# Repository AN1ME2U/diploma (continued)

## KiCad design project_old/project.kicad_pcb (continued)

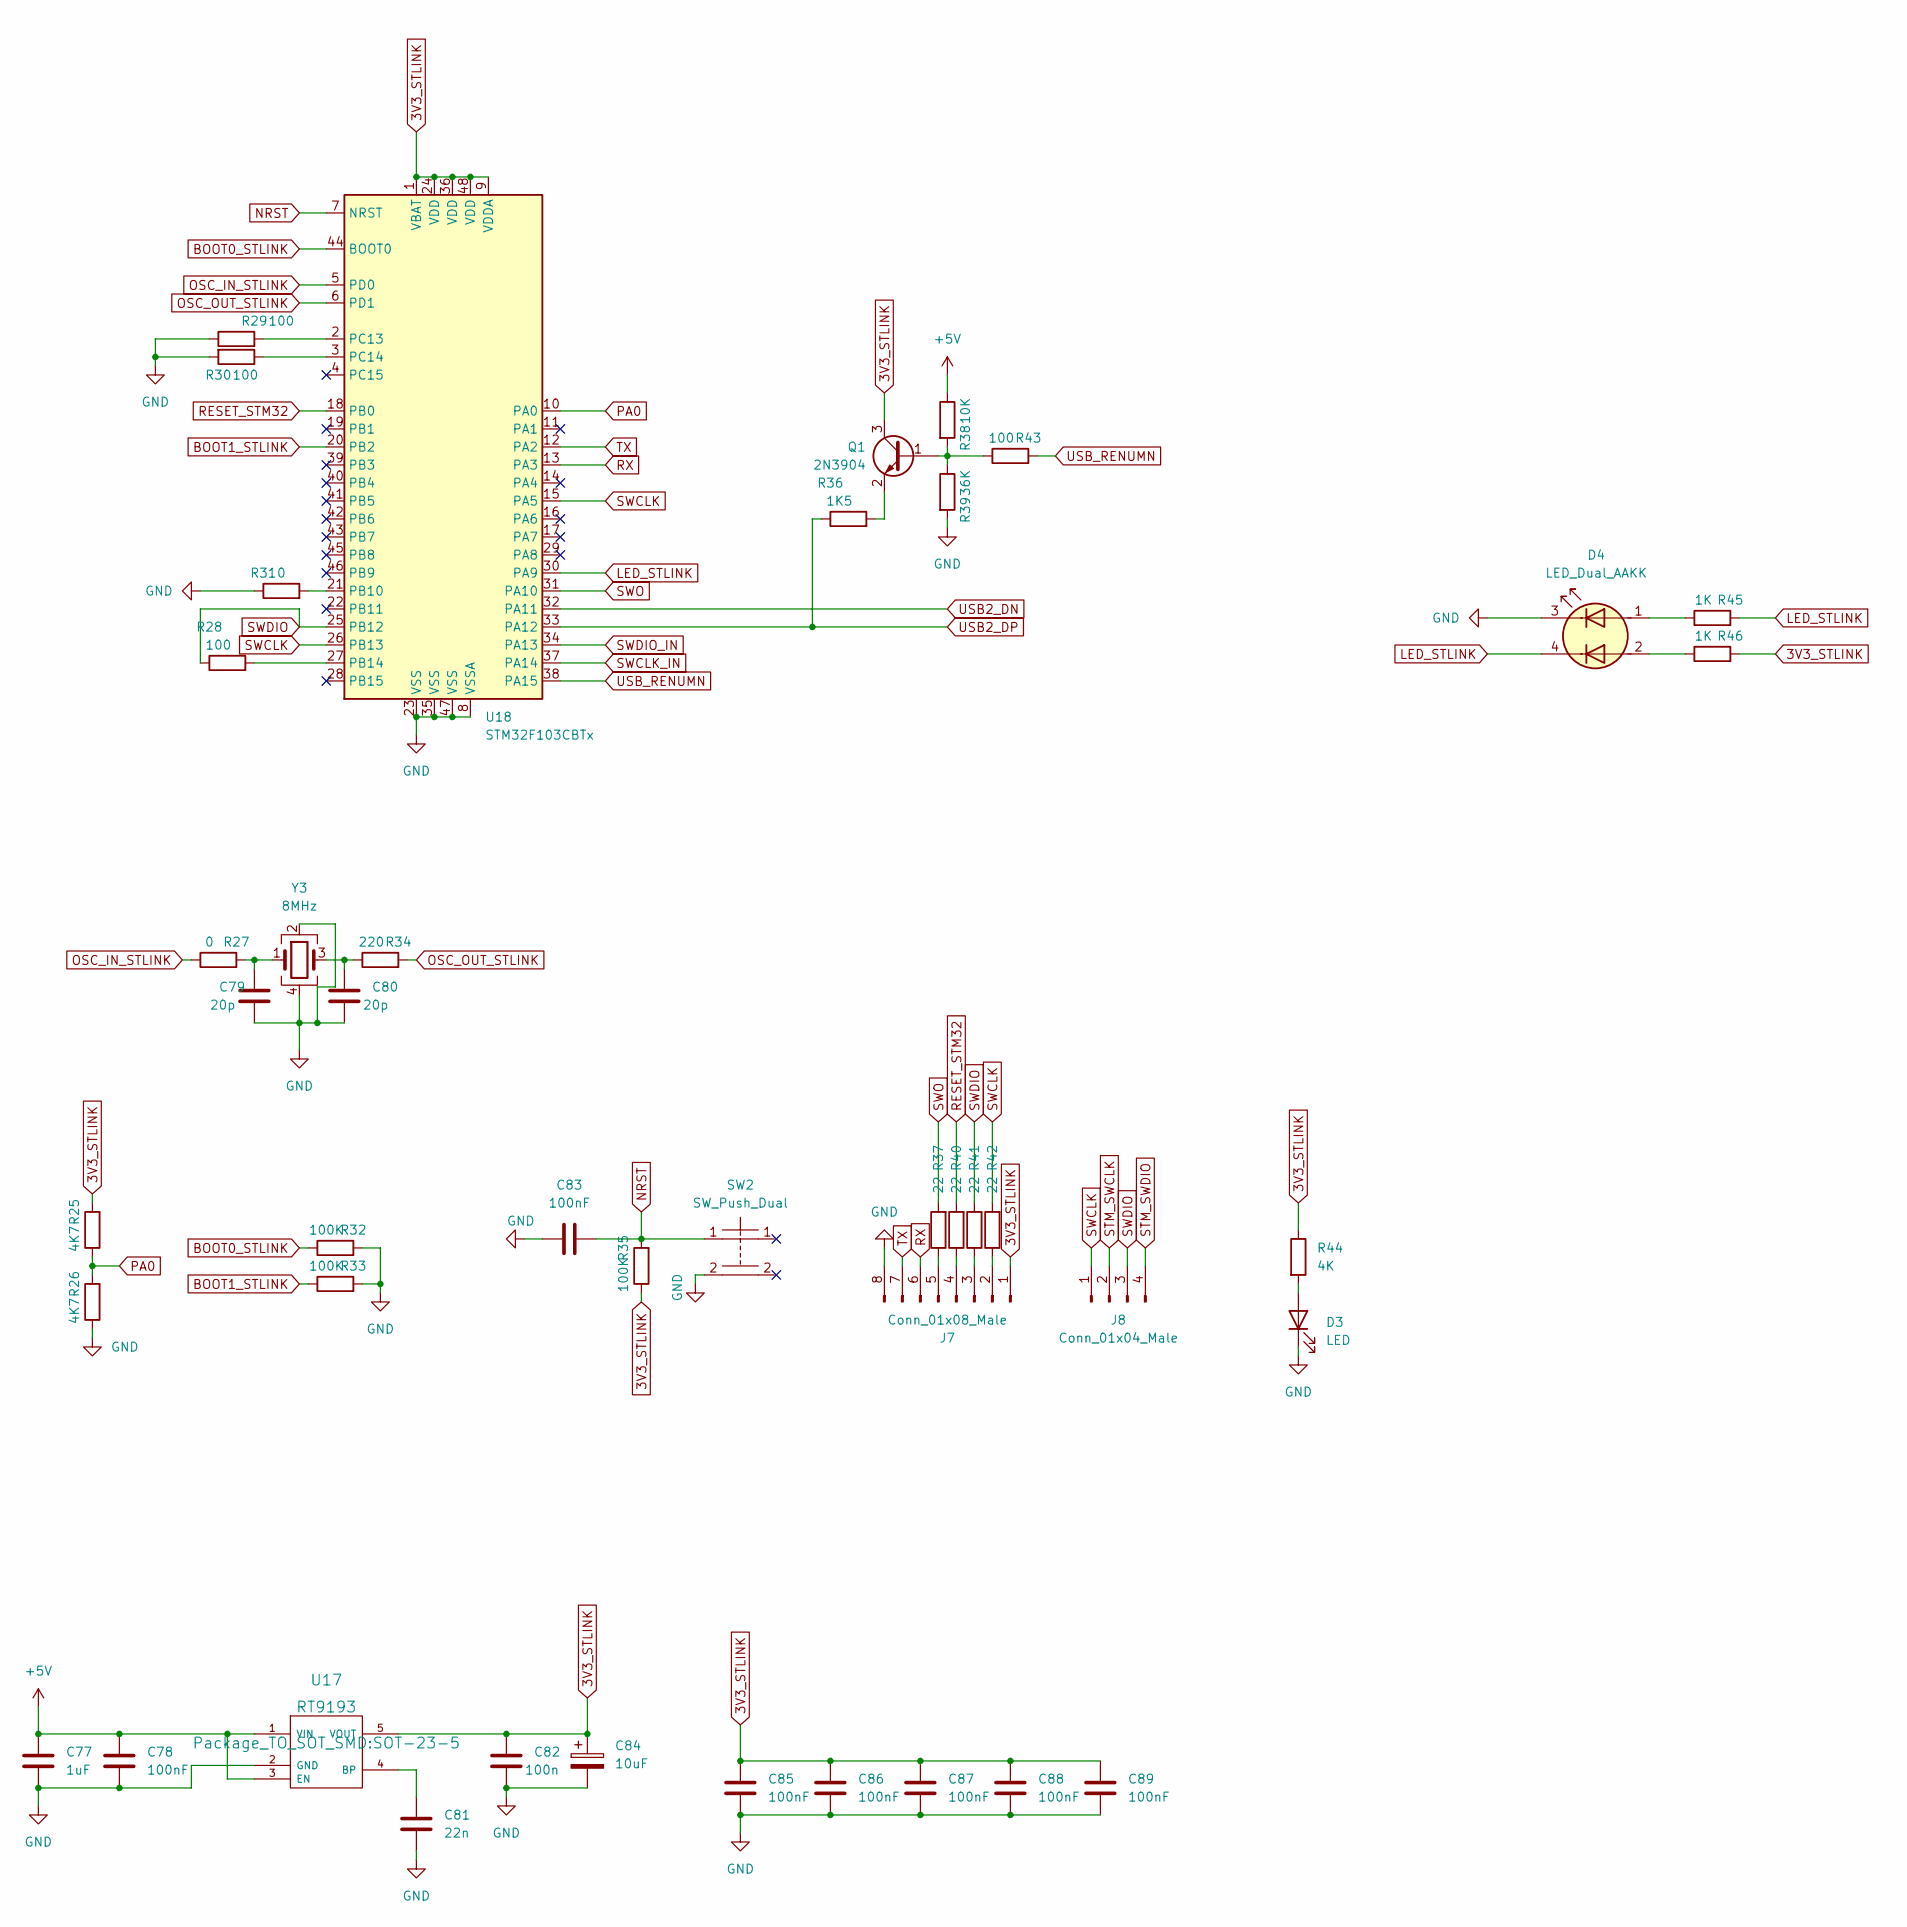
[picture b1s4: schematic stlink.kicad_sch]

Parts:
C77: 1uF; C_0805_2012Metric_Pad1.18x1.45mm_HandSolder
C78: 100nF; C_0805_2012Metric_Pad1.18x1.45mm_HandSolder
C79, C80: 20p; C_0603_1608Metric_Pad1.08x0.95mm_HandSolder
C81: 22n; C_0805_2012Metric_Pad1.18x1.45mm_HandSolder
C82: 100n; C_0805_2012Metric_Pad1.18x1.45mm_HandSolder
C83, C85, C86, C87, C88, C89: 100nF; C_0603_1608Metric_Pad1.08x0.95mm_HandSolder
C84: 10uF; CP_EIA-1608-08_AVX-J
D3: LED; LED_0805_2012Metric_Pad1.15x1.40mm_HandSolder
D4: LED_Dual_AAKK; LED_RGB_Wuerth-PLCC4_3.2x2.8mm_150141M173100
J7: Conn_01x08_Male; PinSocket_1x08_P2.54mm_Vertical
J8: Conn_01x04_Male; PinSocket_1x04_P2.54mm_Vertical
Q1: 2N3904; SOT-23
R25, R26: 4K7; R_0603_1608Metric_Pad0.98x0.95mm_HandSolder
R27, R31: 0; R_0603_1608Metric_Pad0.98x0.95mm_HandSolder
R28, R29, R30, R43: 100; R_0603_1608Metric_Pad0.98x0.95mm_HandSolder
R32, R33, R35: 100K; R_0603_1608Metric_Pad0.98x0.95mm_HandSolder
R34: 220; R_0603_1608Metric_Pad0.98x0.95mm_HandSolder
R36: 1K5; R_0603_1608Metric_Pad0.98x0.95mm_HandSolder
R37, R40, R41, R42: 22; R_0603_1608Metric_Pad0.98x0.95mm_HandSolder
R38: 10K; R_0603_1608Metric_Pad0.98x0.95mm_HandSolder
R39: 36K; R_0603_1608Metric_Pad0.98x0.95mm_HandSolder
R44: 4K; R_0603_1608Metric_Pad0.98x0.95mm_HandSolder
R45, R46: 1K; R_0603_1608Metric_Pad0.98x0.95mm_HandSolder
SW2: SW_Push_Dual; SW_Push_1P1T_NO_6x6mm_H9.5mm
U17: RT9193; SOT-23-5
U18: STM32F103CBTx; LQFP-48_7x7mm_P0.5mm
Y3: 8MHz; Crystal_SMD_3225-4Pin_3.2x2.5mm

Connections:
3V3_STLINK: C82.1, C84.1, C85.1, C86.1, C87.1, C88.1, C89.1, J7.1, Q1.3 (C), R25.2, R35.1, R44.1, R46.2, U17.5 (VOUT), U18.1 (VBAT), U18.9 (VDDA), U18.24 (VDD), U18.36 (VDD), U18.48 (VDD)
+5V: C77.1, C78.1, R38.1, U17.1 (VIN), U17.3 (EN); also elsewhere on the board
BOOT0_STLINK: R32.1, U18.44 (BOOT0)
BOOT1_STLINK: R33.1, U18.20 (PB2)
GND: C77.2, C78.2, C79.2, C80.2, C81.2, C82.2, C83.1, C84.2, C85.2, C86.2, C87.2, C88.2, C89.2, D3.1 (K), D4.3 (K1), J7.8, R26.1, R29.1, R30.2, R31.1, R32.2, R33.2, R39.2, SW2.2, U17.2 (GND), U18.8 (VSSA), U18.23 (VSS), U18.35 (VSS), U18.47 (VSS), Y3.2, Y3.4; also elsewhere on the board
LED_STLINK: D4.4 (K2), R45.2, U18.30 (PA9)
NRST: C83.2, R35.2, SW2.1, U18.7 (NRST)
unnamed: C79.1, R27.2, Y3.1
unnamed: C80.1, R34.1, Y3.3
unnamed: C81.1, U17.4 (BP)
unnamed: D3.2 (A), R44.2
unnamed: D4.1 (A1), R45.1
unnamed: D4.2 (A2), R46.1
unnamed: J7.2, R42.1
unnamed: J7.3, R41.1
unnamed: J7.4, R40.1
unnamed: J7.5, R37.1
unnamed: Q1.1 (B), R38.2, R39.1, R43.1
unnamed: Q1.2 (E), R36.2
unnamed: R28.2, U18.27 (PB14)
unnamed: R29.2, U18.2 (PC13)
unnamed: R30.1, U18.3 (PC14)
unnamed: R31.2, U18.21 (PB10)
OSC_IN_STLINK: R27.1, U18.5 (PD0)
OSC_OUT_STLINK: R34.2, U18.6 (PD1)
PA0: R25.1, R26.2, U18.10 (PA0); also elsewhere on the board
RX: J7.6, U18.13 (PA3)
STM_SWCLK: J8.2; also elsewhere on the board
STM_SWDIO: J8.4; also elsewhere on the board
SWCLK: J8.1, R42.2, U18.15 (PA5), U18.26 (PB13); also elsewhere on the board
SWCLK_IN: U18.37 (PA14); also elsewhere on the board
SWDIO: J8.3, R28.1, R41.2, U18.25 (PB12); also elsewhere on the board
SWDIO_IN: U18.34 (PA13); also elsewhere on the board
SWO: R37.2, U18.31 (PA10); also elsewhere on the board
TX: J7.7, U18.12 (PA2)
USB2_DN: U18.32 (PA11); also elsewhere on the board
USB2_DP: R36.1, U18.33 (PA12); also elsewhere on the board
USB_RENUMN: R43.2, U18.38 (PA15)

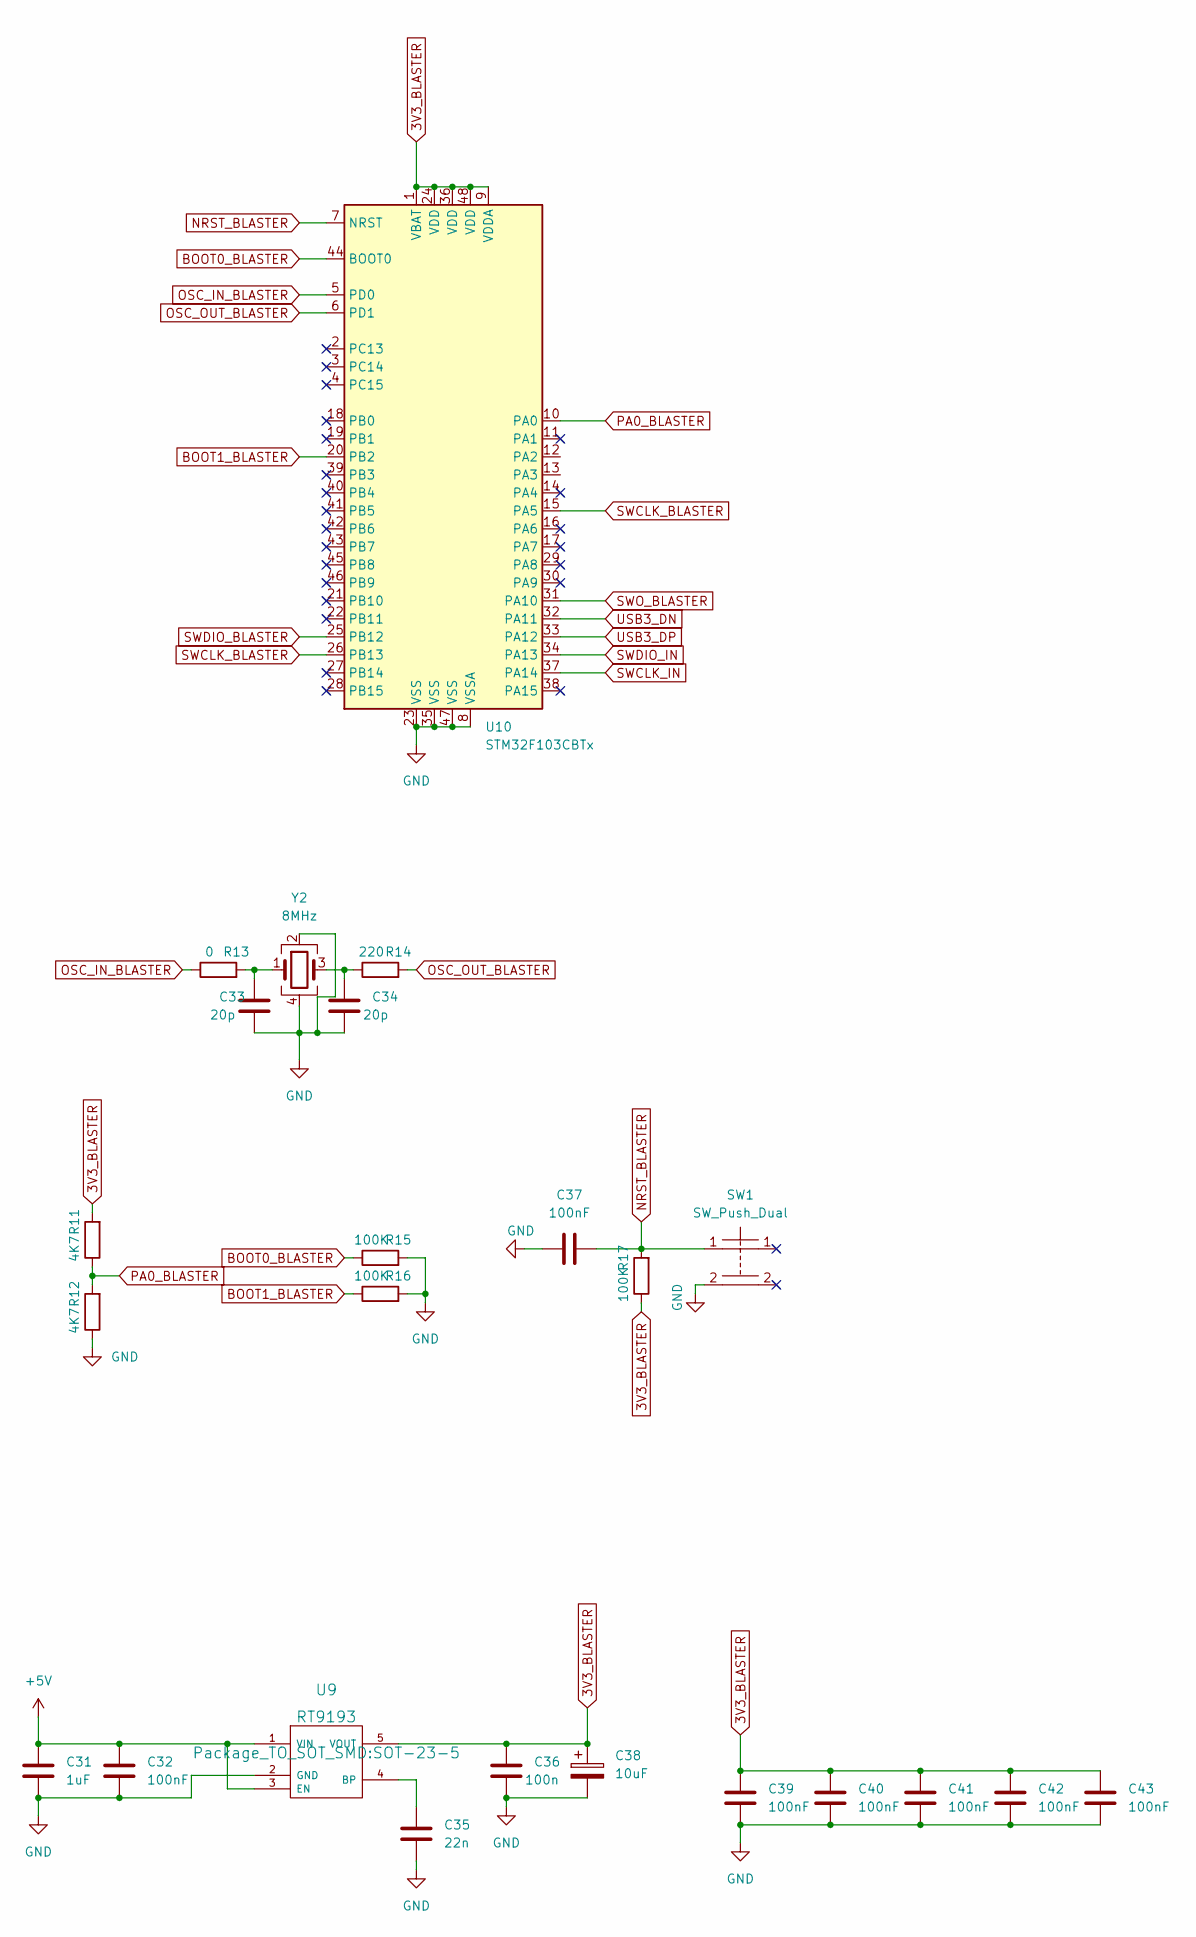
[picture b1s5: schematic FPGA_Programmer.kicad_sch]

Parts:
C31: 1uF; C_0805_2012Metric_Pad1.18x1.45mm_HandSolder
C32: 100nF; C_0805_2012Metric_Pad1.18x1.45mm_HandSolder
C33, C34: 20p; C_0603_1608Metric_Pad1.08x0.95mm_HandSolder
C35: 22n; C_0805_2012Metric_Pad1.18x1.45mm_HandSolder
C36: 100n; C_0805_2012Metric_Pad1.18x1.45mm_HandSolder
C37, C39, C40, C41, C42, C43: 100nF; C_0603_1608Metric_Pad1.08x0.95mm_HandSolder
C38: 10uF; CP_EIA-1608-08_AVX-J
R11, R12: 4K7; R_0603_1608Metric_Pad0.98x0.95mm_HandSolder
R13: 0; R_0603_1608Metric_Pad0.98x0.95mm_HandSolder
R14: 220; R_0603_1608Metric_Pad0.98x0.95mm_HandSolder
R15, R16, R17: 100K; R_0603_1608Metric_Pad0.98x0.95mm_HandSolder
SW1: SW_Push_Dual; SW_Push_1P1T_NO_6x6mm_H9.5mm
U9: RT9193; SOT-23-5
U10: STM32F103CBTx; LQFP-48_7x7mm_P0.5mm
Y2: 8MHz; Crystal_SMD_3225-4Pin_3.2x2.5mm

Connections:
3V3_BLASTER: C36.1, C38.1, C39.1, C40.1, C41.1, C42.1, C43.1, R11.2, R17.1, U9.5 (VOUT), U10.1 (VBAT), U10.9 (VDDA), U10.24 (VDD), U10.36 (VDD), U10.48 (VDD)
+5V: C31.1, C32.1, U9.1 (VIN), U9.3 (EN); also elsewhere on the board
BOOT0_BLASTER: R15.1, U10.44 (BOOT0)
BOOT1_BLASTER: R16.1, U10.20 (PB2)
GND: C31.2, C32.2, C33.2, C34.2, C35.2, C36.2, C37.1, C38.2, C39.2, C40.2, C41.2, C42.2, C43.2, R12.1, R15.2, R16.2, SW1.2, U9.2 (GND), U10.8 (VSSA), U10.23 (VSS), U10.35 (VSS), U10.47 (VSS), Y2.2, Y2.4; also elsewhere on the board
NRST_BLASTER: C37.2, R17.2, SW1.1, U10.7 (NRST)
unnamed: C33.1, R13.2, Y2.1
unnamed: C34.1, R14.1, Y2.3
unnamed: C35.1, U9.4 (BP)
OSC_IN_BLASTER: R13.1, U10.5 (PD0)
OSC_OUT_BLASTER: R14.2, U10.6 (PD1)
PA0_BLASTER: R11.1, R12.2, U10.10 (PA0)
SWCLK_BLASTER: U10.15 (PA5), U10.26 (PB13)
SWCLK_IN: U10.37 (PA14); also elsewhere on the board
SWDIO_BLASTER: U10.25 (PB12)
SWDIO_IN: U10.34 (PA13); also elsewhere on the board
SWO_BLASTER: U10.31 (PA10)
USB3_DN: U10.32 (PA11); also elsewhere on the board
USB3_DP: U10.33 (PA12); also elsewhere on the board

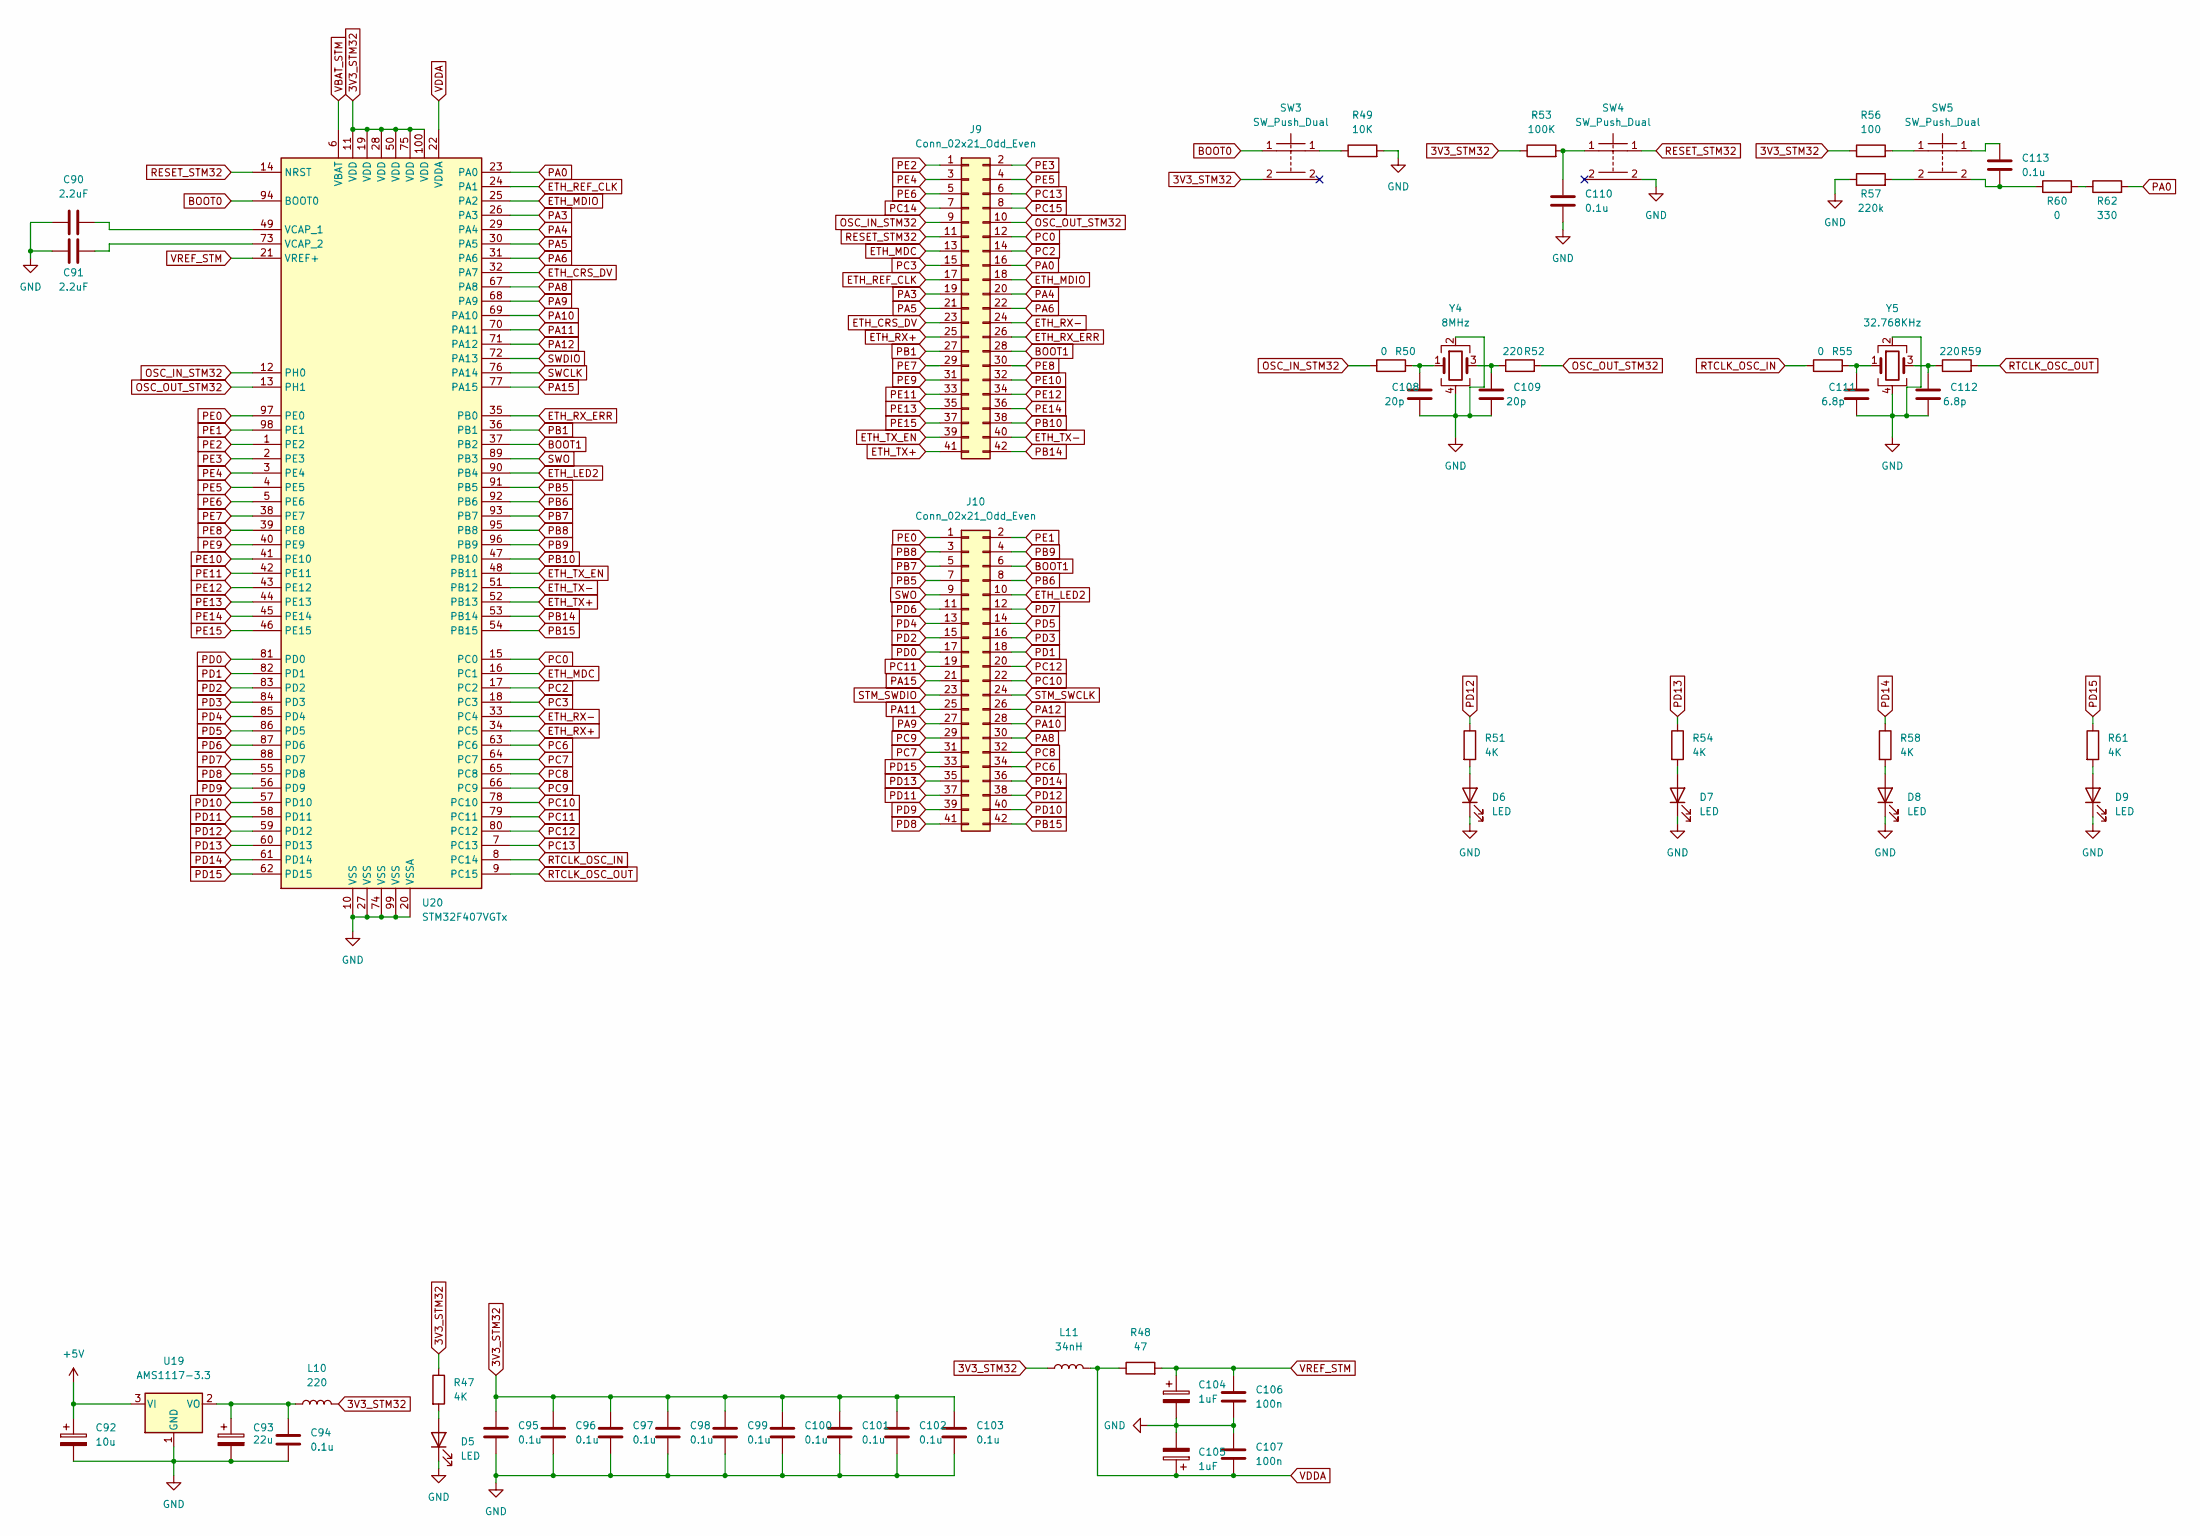
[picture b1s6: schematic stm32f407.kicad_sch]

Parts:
C90, C91: 2.2uF; C_0603_1608Metric_Pad1.08x0.95mm_HandSolder
C92: 10u; CP_EIA-6032-15_Kemet-U_Pad2.25x2.35mm_HandSolder
C93: 22u; CP_EIA-6032-15_Kemet-U_Pad2.25x2.35mm_HandSolder
C94: 0.1u; C_0805_2012Metric_Pad1.18x1.45mm_HandSolder
C95, C96, C97, C98, C99, C100, C101, C102, C103, C110, C113: 0.1u; C_0603_1608Metric_Pad1.08x0.95mm_HandSolder
C104, C105: 1uF; C_0805_2012Metric_Pad1.18x1.45mm_HandSolder
C106, C107: 100n; C_0603_1608Metric_Pad1.08x0.95mm_HandSolder
C108, C109: 20p; C_0603_1608Metric_Pad1.08x0.95mm_HandSolder
C111, C112: 6.8p; C_0603_1608Metric_Pad1.08x0.95mm_HandSolder
D5, D6, D7, D8, D9: LED; LED_0805_2012Metric_Pad1.15x1.40mm_HandSolder
J9, J10: Conn_02x21_Odd_Even; PinHeader_2x21_P2.54mm_Vertical
L10: 220; L_2010_5025Metric_Pad1.52x2.65mm_HandSolder
L11: 34nH; L_0805_2012Metric
R47, R51, R54, R58, R61: 4K; R_0603_1608Metric_Pad0.98x0.95mm_HandSolder
R48: 47; R_0603_1608Metric_Pad0.98x0.95mm_HandSolder
R49: 10K; R_0603_1608Metric_Pad0.98x0.95mm_HandSolder
R50, R55, R60: 0; R_0603_1608Metric_Pad0.98x0.95mm_HandSolder
R52, R59: 220; R_0603_1608Metric_Pad0.98x0.95mm_HandSolder
R53: 100K; R_0603_1608Metric_Pad0.98x0.95mm_HandSolder
R56: 100; R_0603_1608Metric_Pad0.98x0.95mm_HandSolder
R57: 220k; R_0603_1608Metric_Pad0.98x0.95mm_HandSolder
R62: 330; R_0603_1608Metric_Pad0.98x0.95mm_HandSolder
SW3, SW4, SW5: SW_Push_Dual; SW_Push_1P1T_NO_6x6mm_H9.5mm
U19: AMS1117-3.3; SOT-223-3_TabPin2
U20: STM32F407VGTx; LQFP-100_14x14mm_P0.5mm
Y4: 8MHz; Crystal_SMD_3225-4Pin_3.2x2.5mm
Y5: 32.768KHz; Crystal_SMD_3225-4Pin_3.2x2.5mm

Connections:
3V3_STM32: C95.1, C96.1, C97.1, C98.1, C99.1, C100.1, C101.1, C102.1, C103.1, L10.2, L11.1, R47.1, R53.1, R56.1, SW3.2, U20.11 (VDD), U20.19 (VDD), U20.28 (VDD), U20.50 (VDD), U20.75 (VDD), U20.100 (VDD)
+5V: C92.1, U19.3 (VI); also elsewhere on the board
BOOT1: J9.28, J10.6, U20.37 (PB2)
ETH_CRS_DV: J9.23, U20.32 (PA7); also elsewhere on the board
ETH_LED2: J10.10, U20.90 (PB4); also elsewhere on the board
ETH_MDC: J9.13, U20.16 (PC1); also elsewhere on the board
ETH_MDIO: J9.18, U20.25 (PA2); also elsewhere on the board
ETH_REF_CLK: J9.17, U20.24 (PA1); also elsewhere on the board
ETH_RX+: J9.25, U20.34 (PC5); also elsewhere on the board
ETH_RX-: J9.24, U20.33 (PC4); also elsewhere on the board
ETH_RX_ERR: J9.26, U20.35 (PB0); also elsewhere on the board
ETH_TX+: J9.41, U20.52 (PB13); also elsewhere on the board
ETH_TX-: J9.40, U20.51 (PB12); also elsewhere on the board
ETH_TX_EN: J9.39, U20.48 (PB11); also elsewhere on the board
GND: C90.1, C91.2, C92.2, C93.2, C94.2, C95.2, C96.2, C97.2, C98.2, C99.2, C100.2, C101.2, C102.2, C103.2, C104.2, C105.2, C106.2, C107.1, C108.2, C109.2, C110.2, C111.2, C112.2, D5.1 (K), D6.1 (K), D7.1 (K), D8.1 (K), D9.1 (K), R49.2, R57.1, SW4.2, U19.1 (GND), U20.10 (VSS), U20.20 (VSSA), U20.27 (VSS), U20.74 (VSS), U20.99 (VSS), Y4.2, Y4.4, Y5.2, Y5.4; also elsewhere on the board
unnamed: C90.2, U20.49 (VCAP_1)
unnamed: C91.1, U20.73 (VCAP_2)
unnamed: C93.1, C94.1, L10.1, U19.2 (VO)
unnamed: C108.1, R50.2, Y4.1
unnamed: C109.1, R52.1, Y4.3
unnamed: C111.1, R55.2, Y5.1
unnamed: C112.1, R59.1, Y5.3
unnamed: D5.2 (A), R47.2
unnamed: D6.2 (A), R51.2
unnamed: D7.2 (A), R54.2
unnamed: D8.2 (A), R58.2
unnamed: D9.2 (A), R61.2
unnamed: R60.2, R62.1
OSC_IN_STM32: J9.9, R50.1, U20.12 (PH0)
OSC_OUT_STM32: J9.10, R52.2, U20.13 (PH1)
PA0: J9.16, R62.2, U20.23 (PA0); also elsewhere on the board
PA3: J9.19, U20.26 (PA3)
PA4: J9.20, U20.29 (PA4)
PA5: J9.21, U20.30 (PA5)
PA6: J9.22, U20.31 (PA6)
PA8: J10.30, U20.67 (PA8)
PA9: J10.27, U20.68 (PA9)
PA10: J10.28, U20.69 (PA10)
PA11: J10.25, U20.70 (PA11); also elsewhere on the board
PA12: J10.26, U20.71 (PA12); also elsewhere on the board
PA15: J10.21, U20.77 (PA15)
PB1: J9.27, U20.36 (PB1)
PB5: J10.7, U20.91 (PB5)
PB6: J10.8, U20.92 (PB6)
PB7: J10.5, U20.93 (PB7)
PB8: J10.3, U20.95 (PB8)
PB9: J10.4, U20.96 (PB9)
PB10: J9.38, U20.47 (PB10)
PB14: J9.42, U20.53 (PB14)
PB15: J10.42, U20.54 (PB15)
PC0: J9.12, U20.15 (PC0)
PC2: J9.14, U20.17 (PC2)
PC3: J9.15, U20.18 (PC3)
PC6: J10.34, U20.63 (PC6)
PC7: J10.31, U20.64 (PC7)
PC8: J10.32, U20.65 (PC8)
PC9: J10.29, U20.66 (PC9)
PC10: J10.22, U20.78 (PC10)
PC11: J10.19, U20.79 (PC11)
PC12: J10.20, U20.80 (PC12)
PC13: J9.6, U20.7 (PC13)
PC14: J9.7
PC15: J9.8
PD0: J10.17, U20.81 (PD0)
PD1: J10.18, U20.82 (PD1)
PD2: J10.15, U20.83 (PD2)
PD3: J10.16, U20.84 (PD3)
PD4: J10.13, U20.85 (PD4)
PD5: J10.14, U20.86 (PD5)
PD6: J10.11, U20.87 (PD6); also elsewhere on the board
PD7: J10.12, U20.88 (PD7); also elsewhere on the board
PD8: J10.41, U20.55 (PD8)
PD9: J10.39, U20.56 (PD9)
PD10: J10.40, U20.57 (PD10)
PD11: J10.37, U20.58 (PD11)
PD12: J10.38, R51.1, U20.59 (PD12)
PD13: J10.35, R54.1, U20.60 (PD13)
PD14: J10.36, R58.1, U20.61 (PD14)
PD15: J10.33, R61.1, U20.62 (PD15)
PE0: J10.1, U20.97 (PE0)
PE1: J10.2, U20.98 (PE1)
PE2: J9.1, U20.1 (PE2)
PE3: J9.2, U20.2 (PE3)
PE4: J9.3, U20.3 (PE4)
PE5: J9.4, U20.4 (PE5)
PE6: J9.5, U20.5 (PE6)
PE7: J9.29, U20.38 (PE7)
PE8: J9.30, U20.39 (PE8)
PE9: J9.31, U20.40 (PE9)
PE10: J9.32, U20.41 (PE10)
PE11: J9.33, U20.42 (PE11)
PE12: J9.34, U20.43 (PE12)
PE13: J9.35, U20.44 (PE13)
PE14: J9.36, U20.45 (PE14)
PE15: J9.37, U20.46 (PE15)
RTCLK_OSC_IN: R55.1, U20.8 (PC14)
RTCLK_OSC_OUT: R59.2, U20.9 (PC15)
STM_SWCLK: J10.24; also elsewhere on the board
STM_SWDIO: J10.23; also elsewhere on the board
SWCLK: U20.76 (PA14); also elsewhere on the board
SWDIO: U20.72 (PA13); also elsewhere on the board
SWO: J10.9, U20.89 (PB3); also elsewhere on the board
VBAT_STM: U20.6 (VBAT)
VDDA: C105.1, C107.2, L11.2, R48.1, U20.22 (VDDA)
VREF_STM: C104.1, C106.1, R48.2, U20.21 (VREF+)

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
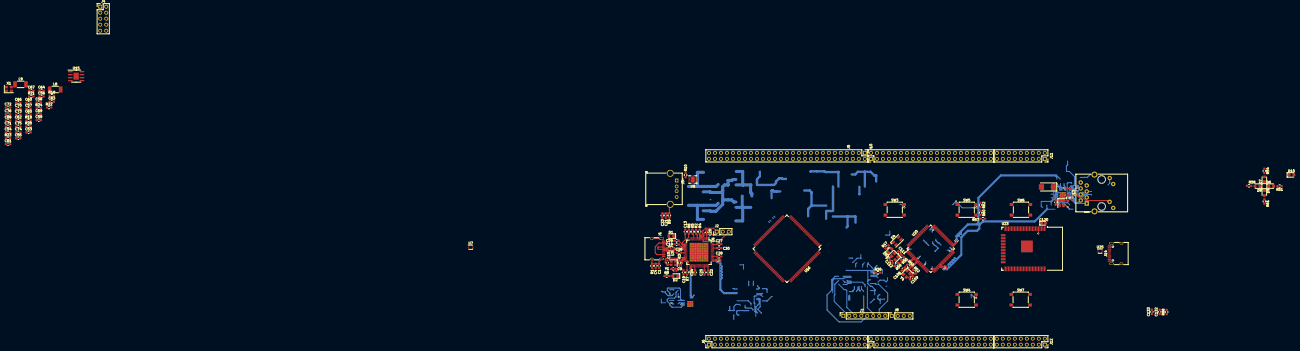
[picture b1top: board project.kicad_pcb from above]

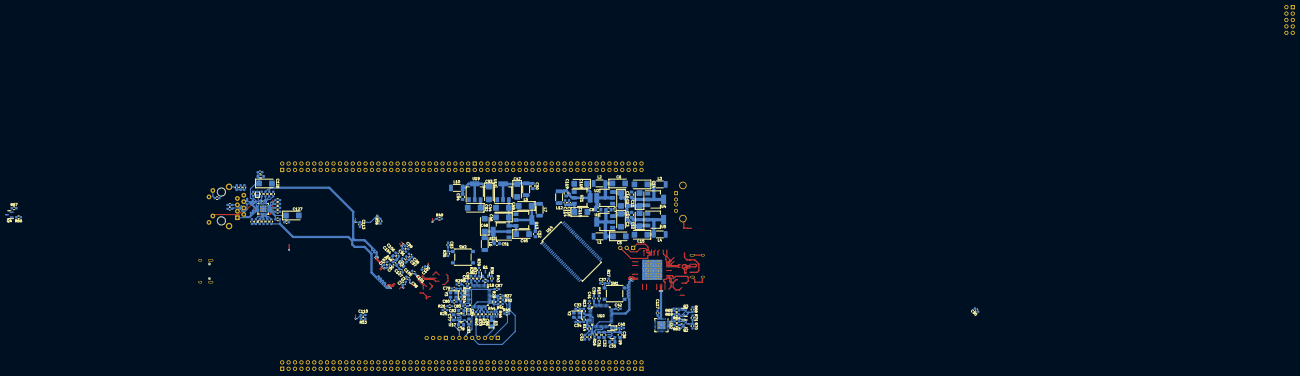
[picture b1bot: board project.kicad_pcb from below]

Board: 4 copper layers, 305 parts (177 on the bottom side), 367 nets.

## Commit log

2022-04-16 Add all done for a moment
2022-05-01 еще одни дополнения
